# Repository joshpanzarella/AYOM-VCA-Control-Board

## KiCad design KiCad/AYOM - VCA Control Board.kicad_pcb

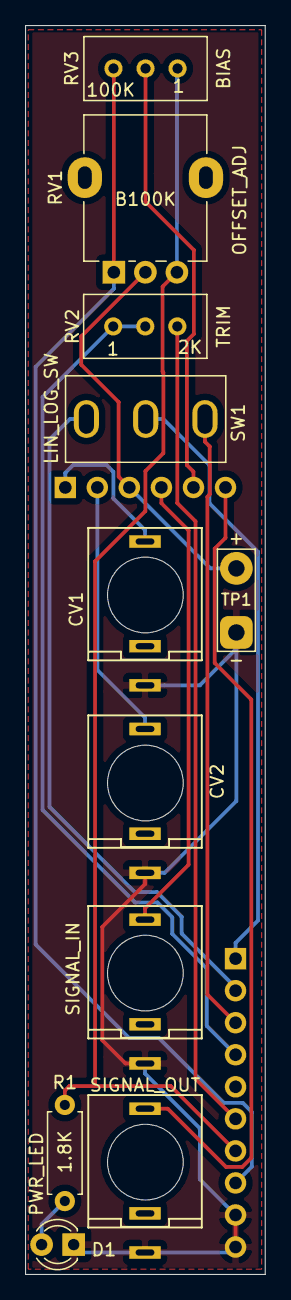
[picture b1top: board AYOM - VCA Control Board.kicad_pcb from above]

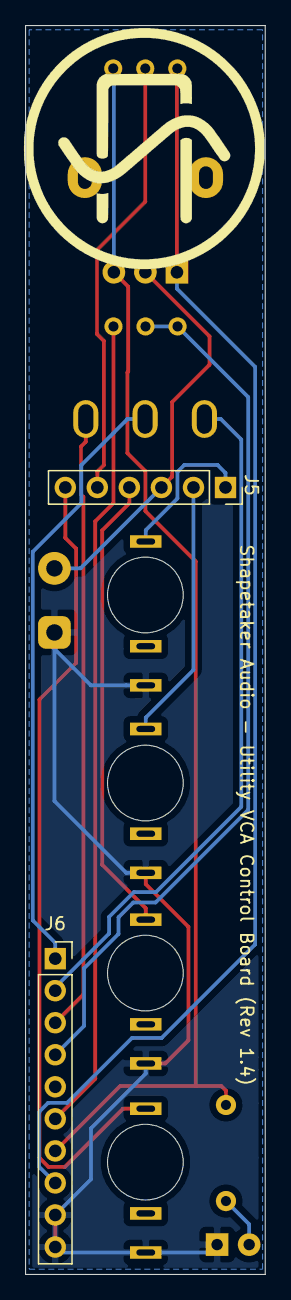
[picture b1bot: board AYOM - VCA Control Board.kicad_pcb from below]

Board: 2 copper layers, 19.0 x 99.0 mm, 13 parts (2 on the bottom side), 15 nets.

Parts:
CV1: CV1; thonkiconn_fuzzySi
CV2: CV2; thonkiconn_fuzzySi
D1: PWR_LED; LED_D3.0mm
J5: CONN_1; PinSocket_1x06_P2.54mm_Vertical
J6: CONN_2; PinSocket_1x10_P2.54mm_Vertical
R1: 1.8K; R_Axial_DIN0207_L6.3mm_D2.5mm_P7.62mm_Horizontal
RV1: OFFSET_ADJ; Potentiometer_Alpha_RD901F-40-00D_Single_Vertical
RV2: TRIM; Potentiometer_Bourns_3296W_Vertical
RV3: BIAS; Potentiometer_Bourns_3296W_Vertical
SIGNAL_IN: SIGNAL_IN; thonkiconn_fuzzySi
SIGNAL_OUT: SIGNAL_OUT; thonkiconn_fuzzySi
SW1: LIN_LOG_SW; Mini_Toggle_Switch_SPDT_ON-ON
TP1: OFFSET_ADJ_TP; TestPoint_2Pads_Pitch5.08mm_Drill1.3mm

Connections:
+12V: J6.7, R1.2, RV1.3, RV3.1
-12V: J6.8, RV1.1, RV3.3
/BIAS: J5.5, RV3.2
/CV1: CV1.3, J5.1
/CV2: CV2.3, J5.2
/LOG_LIN_SW_1: J6.1, SW1.2
/LOG_LIN_SW_2: J6.2, SW1.1
/LOG_LIN_SW_3: J6.3, SW1.3
/OFFSET_ADJ: J5.3, RV1.2, TP1.2
/SIGNAL_IN: J5.4, SIGNAL_IN.3
/SIGNAL_OUT: J5.6, SIGNAL_OUT.3
/TRIM_1: J6.4, RV2.1, RV2.2
/TRIM_3: J6.6, RV2.3
GND: CV1.1, CV2.1, D1.1, J6.9, J6.10, SIGNAL_IN.1, SIGNAL_OUT.1, TP1.1
unnamed: D1.2, R1.1

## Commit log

2020-05-22 Added test point for offset potentiometer
2020-05-24 Updated layout and added SPDT switch model
2020-05-24 Updated Thonkiconn footprints
2020-05-24 Updated silkscreen
2020-05-24 Added renders of PCB
2020-08-08 Restructured repo, added Gerbers, Gerber archive, and SVG exports
2020-08-16 Updated Gerbers and renamed Gerber archive
2020-08-16 Updated Gerber archive
2020-09-10 Updated Gerbers and archive
2020-09-23 Updated Gerbers
2020-09-23 Updated Gerber archive name
2020-10-10 Updated acronyms in filenames
